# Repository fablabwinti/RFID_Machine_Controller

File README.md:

# RFID_Machine_Controller
This repository contains the hardware design files (eagle) and the firmware (Arduino) for the Fablab Winti RFID machine access controller. 
## Hardware features
- Based on ESP8266 so it has direct access to WiFi
- RFID reader 
- OLED display
- Piezo buzzer
- Multi-color LED
- SD card for event logging
- RTC for accurate time keeping without network access
- Isolated output with screw terminal
  - Option 1: Relay output: 250V, 5A, NC or NO with a 5x20mm fuse
  - Option 2: Opto-coupled output (50V, 40mA)
- Input voltage: 5V ±0.5V with input protection (reverse voltage protection, overvoltage protection)
- Three input connecters: 5.5x2.1mm DC jack, Micro USB jack, screw termianl

## Firmware features
- Easy web based configuration
- Time sync through NTP
- Automatic synchronization of local RTC 
- Automatic update of user database from server
- Local storage of access rights: works during network failures
- Local data logging to SD-Card or Flash (TBD)
- Transmit log data to server as soon as it is available

## Arduino IDE
### Add Board to IDE
File -> Preferences -> Settings -> Additional boards manager URLs: http://arduino.esp8266.com/stable/package_esp8266com_index.json  
### Install Board
Tools -> Boards -> Boards Manager
Search for "esp8266" and install it
### Select Board
Tools -> Boards -> esp8622 -> "Generic ESP8622 Module"
### Board Configurations
Select the following settings under "Tools"

### Install Libraries
Unzip "FabLabRFID_Library.zip" in the arduino library folder:

- Windows: `C:\Users\{username}\Documents\Arduino`
- macOS: `/Users/{username}/Documents/Arduino`
- Linux: `/home/{username}/Arduino`

#### Manually

Tools -> Manage Libraries

Install all libraries as described in Fablab_RFID_control.ino, line 52 to 70 (?)

MRFC522: Download from git (https://github.com/miguelbalboa/rfid) and add it to the library (.../Documents/Arduino/Libraries/...)

## Upload Flash Content

The `spiffs_flash.py` script automatically builds the SPIFFS filesystem image from the `data` directory and uploads it to the ESP8266.

### Prerequisites
- Python 3.x installed
- ESP8266 connected via USB
- Arduino15 directory present (auto-detected or manually specified)

### Usage

Basic upload (auto-detects Arduino15 directory):
```bash
python spiffs_flash.py --port COM8
```

With custom options:
```bash
# Specify Arduino15 directory manually
python spiffs_flash.py --port COM8 --arduino-root "C:\Users\YourName\AppData\Local\Arduino15"

# Erase SPIFFS region before writing (if write fails)
python spiffs_flash.py --port COM8 --erase-region

# Keep temporary build files for inspection
python spiffs_flash.py --port COM8 --keep-temp

# Use existing .bin file (skip build)
python spiffs_flash.py --port COM8 --bin path\to\existing.spiffs.bin
```

### Troubleshooting
- If Arduino15 not found, the script will prompt for the path
- Use `--erase-region` if you encounter write errors (preserves main firmware)
- Change COM port number to match your device (check Device Manager on Windows)

# License
-Firmware under GNU LGPL Version 3
-Hardware under Creative Commons 4.0 license: CC-BY-SA

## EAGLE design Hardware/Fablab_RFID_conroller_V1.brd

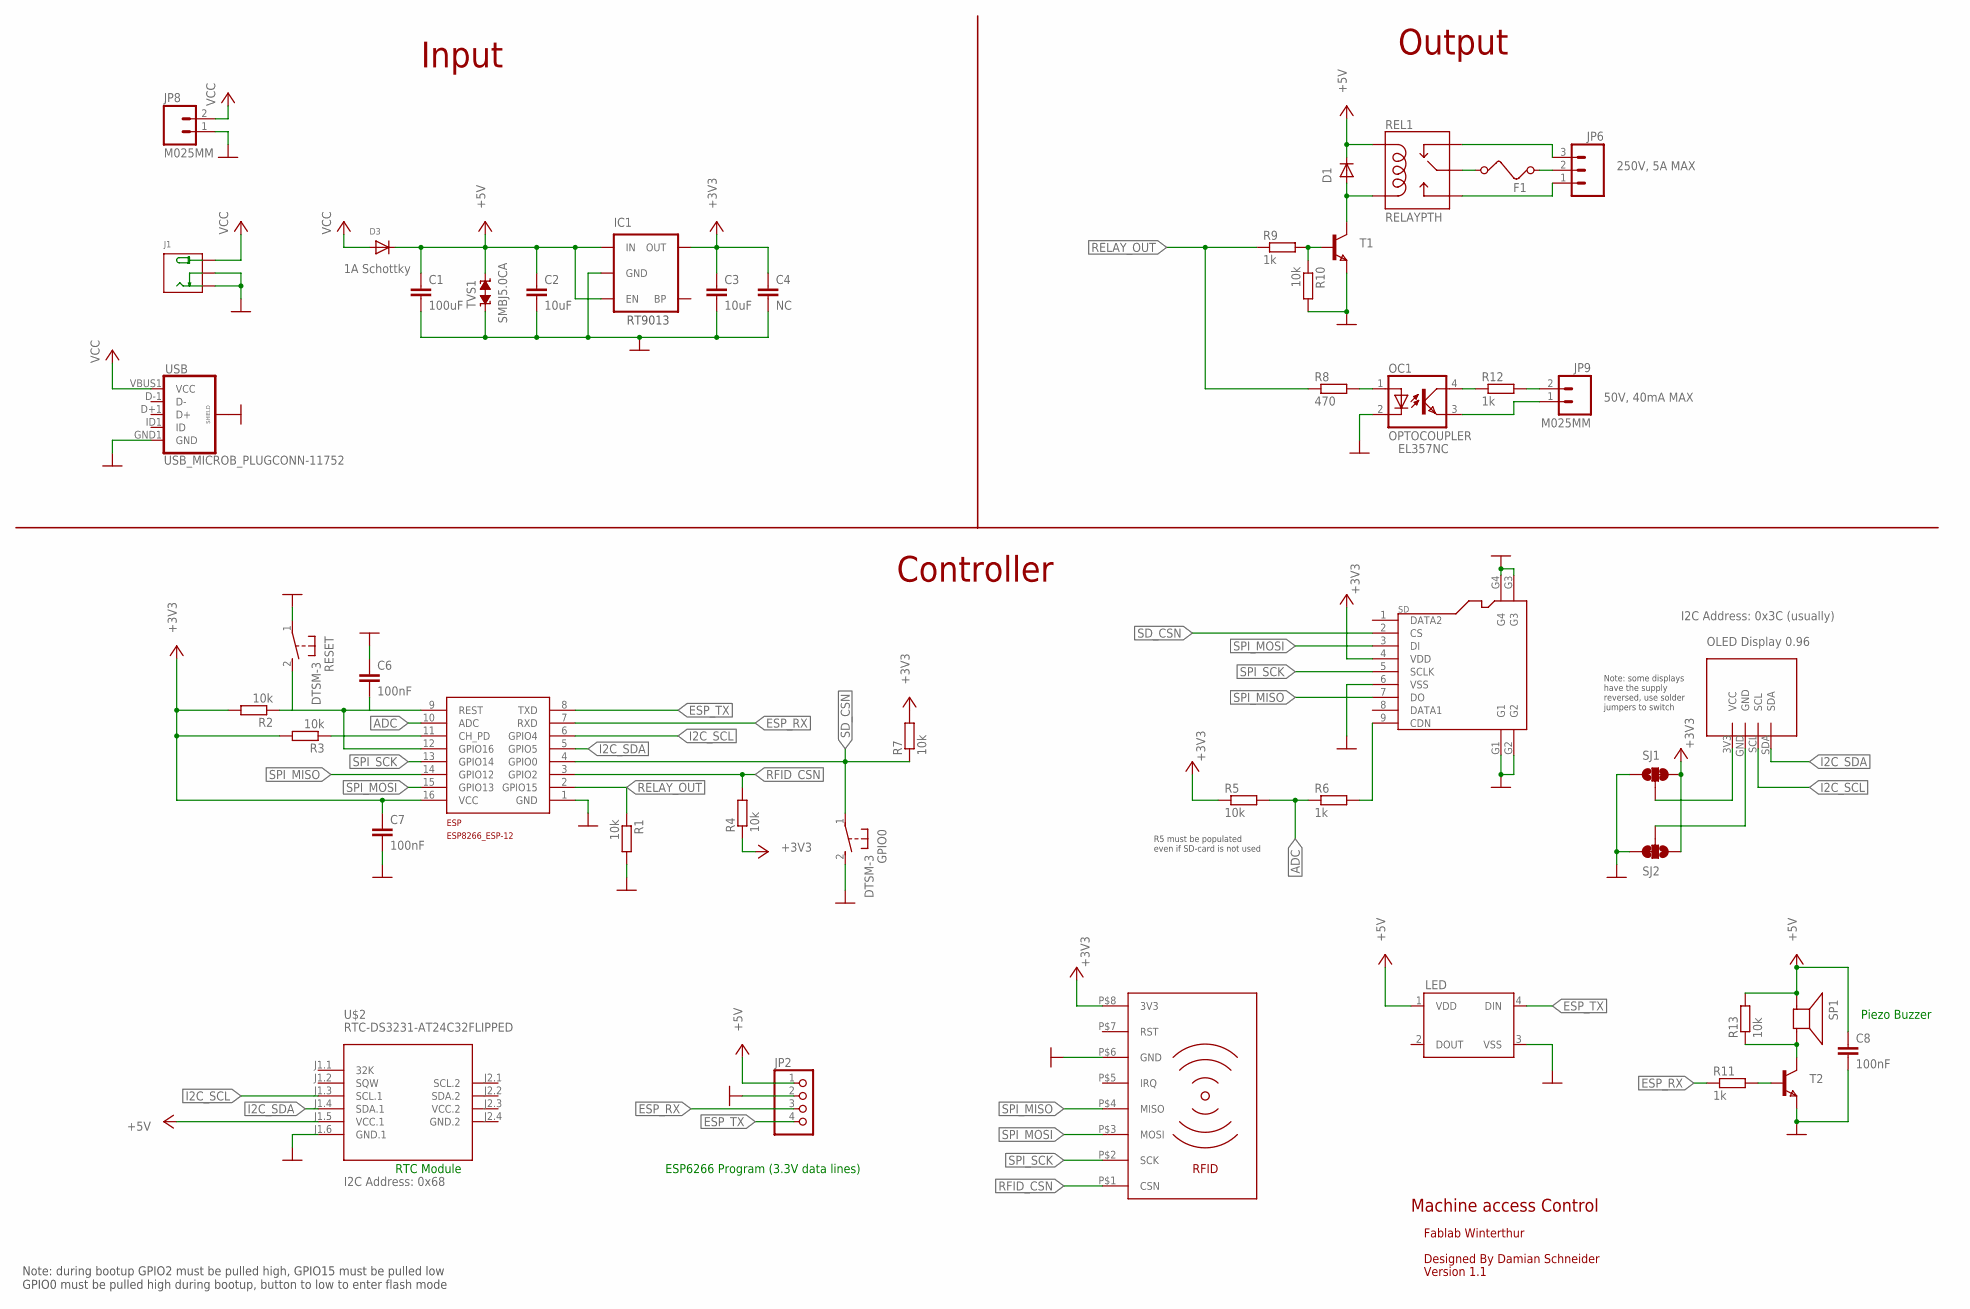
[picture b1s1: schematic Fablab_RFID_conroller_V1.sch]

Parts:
C1: 100uF; C1206
C2, C3: 10uF; C0805
C4: NC; C1206
C6, C7, C8: 100nF; C0603
D1: DIODE-MINIMELF; MINIMELF
D3: DIODESMA; SMADIODE
ESP: ESP8266_ESP-12; ESP8266-ESP12
F1: FUSE
GPIO0: DTSM-3
IC1: V_REG_LDOSMD; SOT23-5
J1: JACK-DC-3P-3410020P1; PW-3P-2.1
JP2: HEADER-1X476MIL; 1X04_ROUND_76
JP6: M03-SCREW-5MM; SCREWTERMINAL-5MM-3
JP8, JP9: M025MM; SCREWTERMINAL-5MM-2
LED: WS2812B
OC1: OPTOCOUPLER; SOP04
OLED: OLED_0.96_I2CNOHOLES; OLED_0.96_I2C_NOHOLES
R1, R2, R3, R4, R5, R7, R10, R13: 10k; R0603
R6, R9, R11: 1k; R0603
R8: 470; R0603
R12: 1k; R0805
REL1: RELAYPTH; SRD-05VDC-SL-C
RESET: DTSM-3
RFID: RFID_MODULE_RC522; RFID-RC522-MODULE
SD: MICRO-SDCARD-CONNECTOR-3300060P1; 9P-SMD-W-RING
SJ1, SJ2: JUMPER-PAD-3-2OF3_NC_BY_TRACE_LARGE; PAD-JUMPER-3-2OF3_NC_BY_TRACE_YES_SILK_LARGE
SP1: SPEAKER/AL60P; AL60P
T1, T2: NPNSOT23; SOT-23
TVS1: TVS-SMBJ; SMBJ
U$2: RTC-DS3231-AT24C32FLIPPED; RTC-DS3231_FLIPPED
USB: USB_MICROB_PLUGCONN-11752; USB-B-MICRO-SMD_V03

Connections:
!SDCARD_DETECT: R6.2, SD.9 (CDN)
+3V3: C3.1, C4.1, C7.1, ESP.16 (VCC), IC1.5 (OUT), R2.2, R3.2, R4.1, R5.1, R7.2, RFID.P$8 (3V3), SD.4 (VDD), SJ1.3, SJ2.1
+5V: C1.1, C2.1, C8.1, D1.C, D3.C, IC1.1 (IN), IC1.3 (EN), JP2.1, LED.1 (VDD), R13.2, REL1.COIL1, SP1.1 (+), TVS1.C (2), U$2.J1.5 (VCC.1)
ADC: ESP.10 (ADC), R5.2, R6.1
CHPD: ESP.11 (CH_PD), R3.1
ESP_RX: ESP.7 (RXD), JP2.3, R11.1
ESP_TX: ESP.8 (TXD), JP2.4, LED.4 (DIN)
GND: C1.2, C2.2, C3.2, C4.2, C6.1, C7.2, C8.2, ESP.1 (GND), GPIO0.2, IC1.2 (GND), J1.-1 (-), J1.-2 (CDN), JP2.2, JP8.1, LED.3 (VSS), OC1.2 (C), R1.2, R10.2, RESET.1, RFID.P$6 (GND), SD.6 (VSS), SD.G1, SD.G2, SD.G3, SD.G4, SJ1.1, SJ2.3, T1.2 (E), T2.2 (E), TVS1.A (1), U$2.J1.6 (GND.1), USB.GND1 (GND), USB.SHIELD1 (SHIELD), USB.SHIELD2 (SHIELD), USB.SHIELD3 (SHIELD)
GND.2: U$2.J2.4 (GND.2)
I2C_SCL: ESP.6 (GPIO4), OLED.SCL, U$2.J1.3 (SCL.1)
I2C_SDA: ESP.5 (GPIO5), OLED.SDA, U$2.J1.4 (SDA.1)
unnamed: JP9.2, R12.2
unnamed: OLED.3V3 (VCC), SJ1.2
unnamed: OLED.GND, SJ2.2
unnamed: R9.2, R10.1, T1.3 (B)
unnamed: D1.A, REL1.COIL0, T1.1 (C)
unnamed: R13.1, SP1.2 (-), T2.1 (C)
unnamed: R11.2, T2.3 (B)
unnamed: F1.1, JP6.2
unnamed: JP6.1, REL1.SW_NO (SWOPEN)
unnamed: F1.2, REL1.SWCOMMON
unnamed: JP6.3, REL1.SW_NC (SWCLOSE)
unnamed: OC1.1 (A), R8.2
unnamed: OC1.4 (COL), R12.1
unnamed: JP9.1, OC1.3 (EMIT)
RELAY_OUT: ESP.2 (GPIO15), R1.1, R8.1, R9.1
RESET: C6.2, ESP.9 (REST), ESP.12 (GPIO16), R2.1, RESET.2
RFID_CSN: ESP.3 (GPIO2), R4.2, RFID.P$1 (CSN)
SD_CSN: ESP.4 (GPIO0), GPIO0.1, R7.1, SD.2 (CS)
SPI_MISO: ESP.14 (GPIO12), RFID.P$4 (MISO), SD.7 (DO)
SPI_MOSI: ESP.15 (GPIO13), RFID.P$3 (MOSI), SD.3 (DI)
SPI_SCK: ESP.13 (GPIO14), RFID.P$2 (SCK), SD.5 (SCLK)
VCC: D3.A, J1.+, JP8.2, USB.VBUS1 (VCC)
VCC.2: U$2.J2.3 (VCC.2)

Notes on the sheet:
ESP6266 Program (3.3V data lines)
Note: during bootup GPIO2 must be pulled high, GPIO15 must be pulled low GPIO0 must be pulled high during bootup, button to low to enter flash mode
Piezo Buzzer
OLED Display 0.96
R5 must be populated even if SD-card is not used
RTC Module
RT9013
Machine access Control
Fablab Winterthur
Designed By Damian Schneider
EL357NC
50V, 40mA MAX
250V, 5A MAX
I2C Address: 0x68
I2C Address: 0x3C (usually)
1A Schottky
SMBJ5.0CA
Input
Output
Controller
Note: some displays have the supply reversed, use solder jumpers to switch
Version 1.1

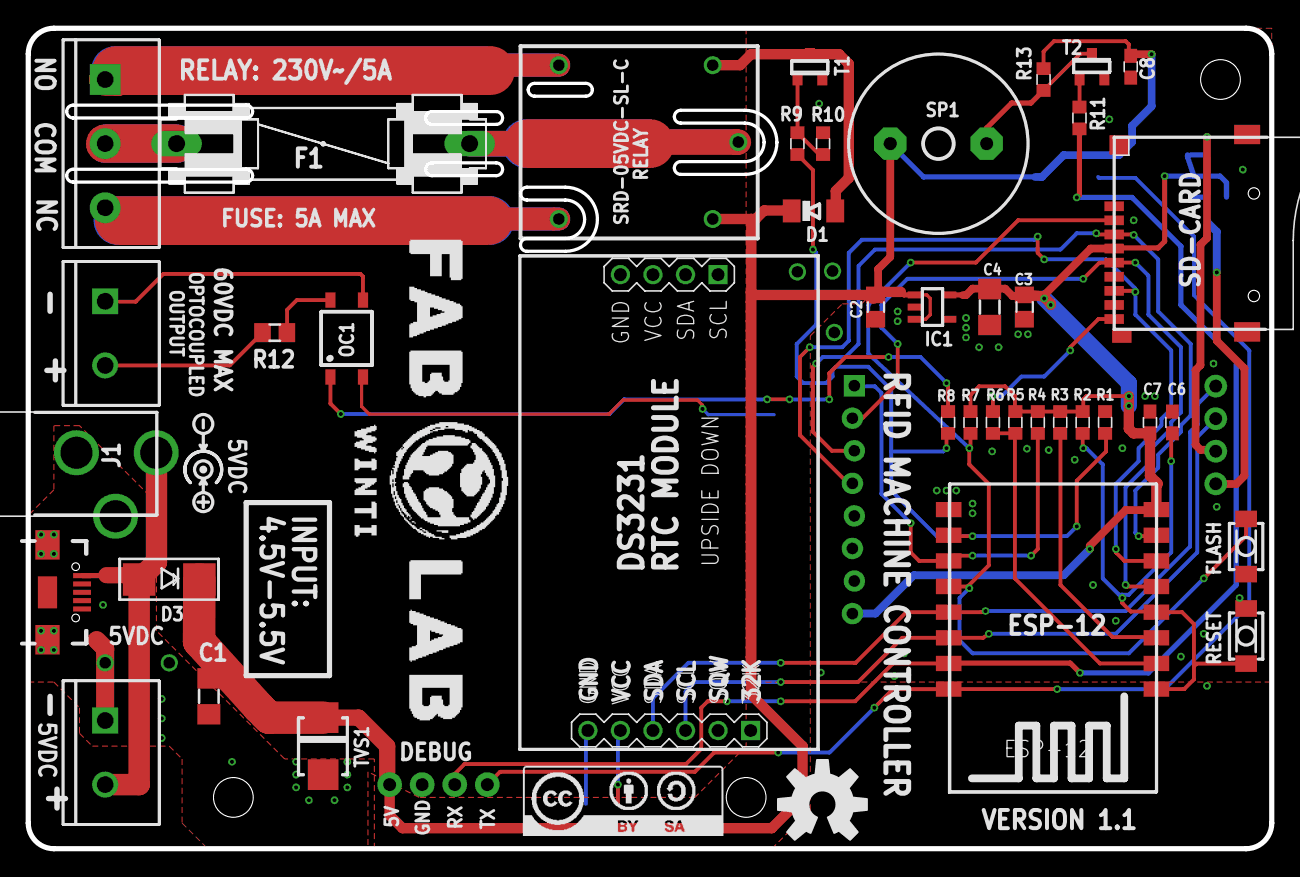
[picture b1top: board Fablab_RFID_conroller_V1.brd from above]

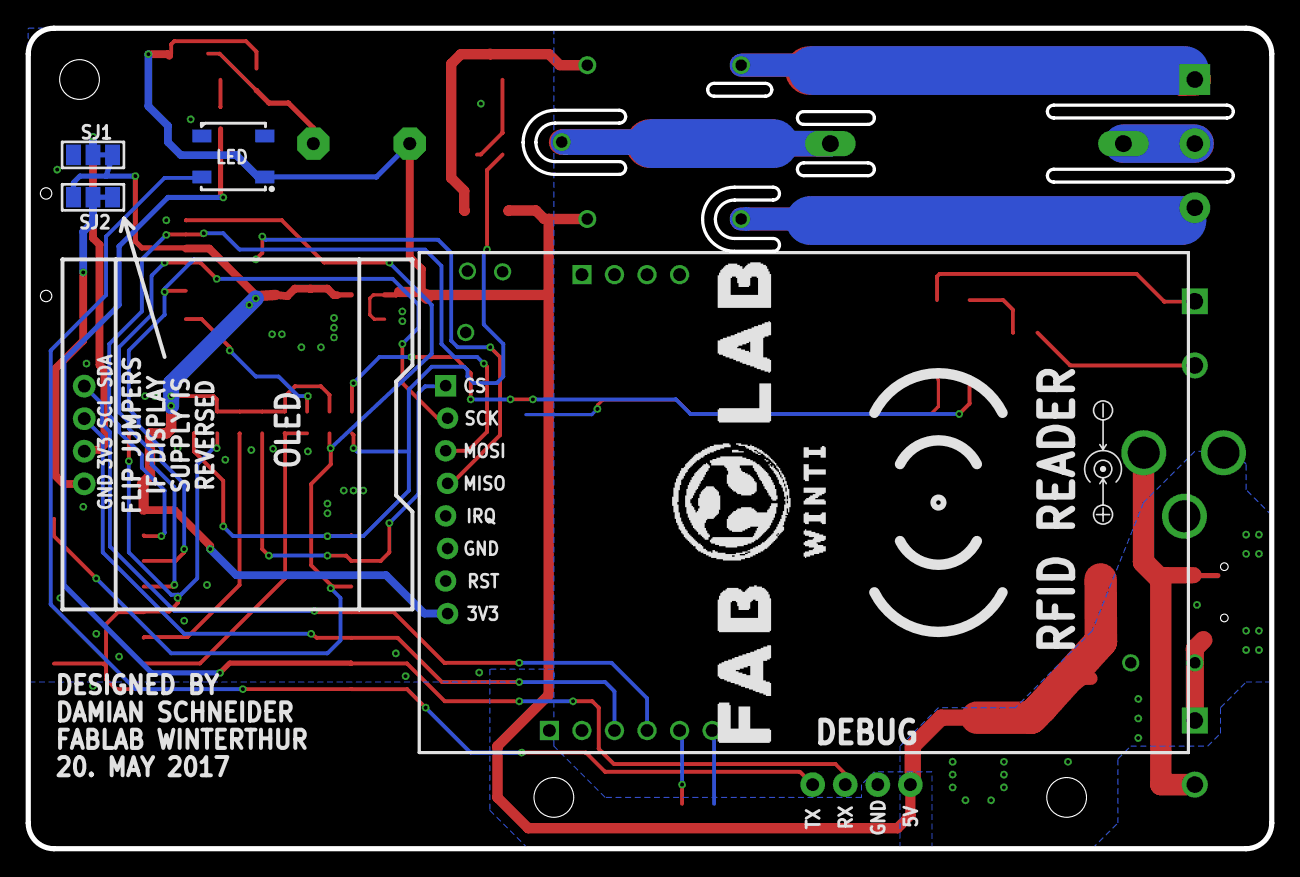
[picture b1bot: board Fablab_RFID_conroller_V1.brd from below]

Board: 2 copper layers, 97.0 x 64.0 mm, 47 parts (5 on the bottom side), 32 nets.

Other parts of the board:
U$6: OSHW-LOGO-L

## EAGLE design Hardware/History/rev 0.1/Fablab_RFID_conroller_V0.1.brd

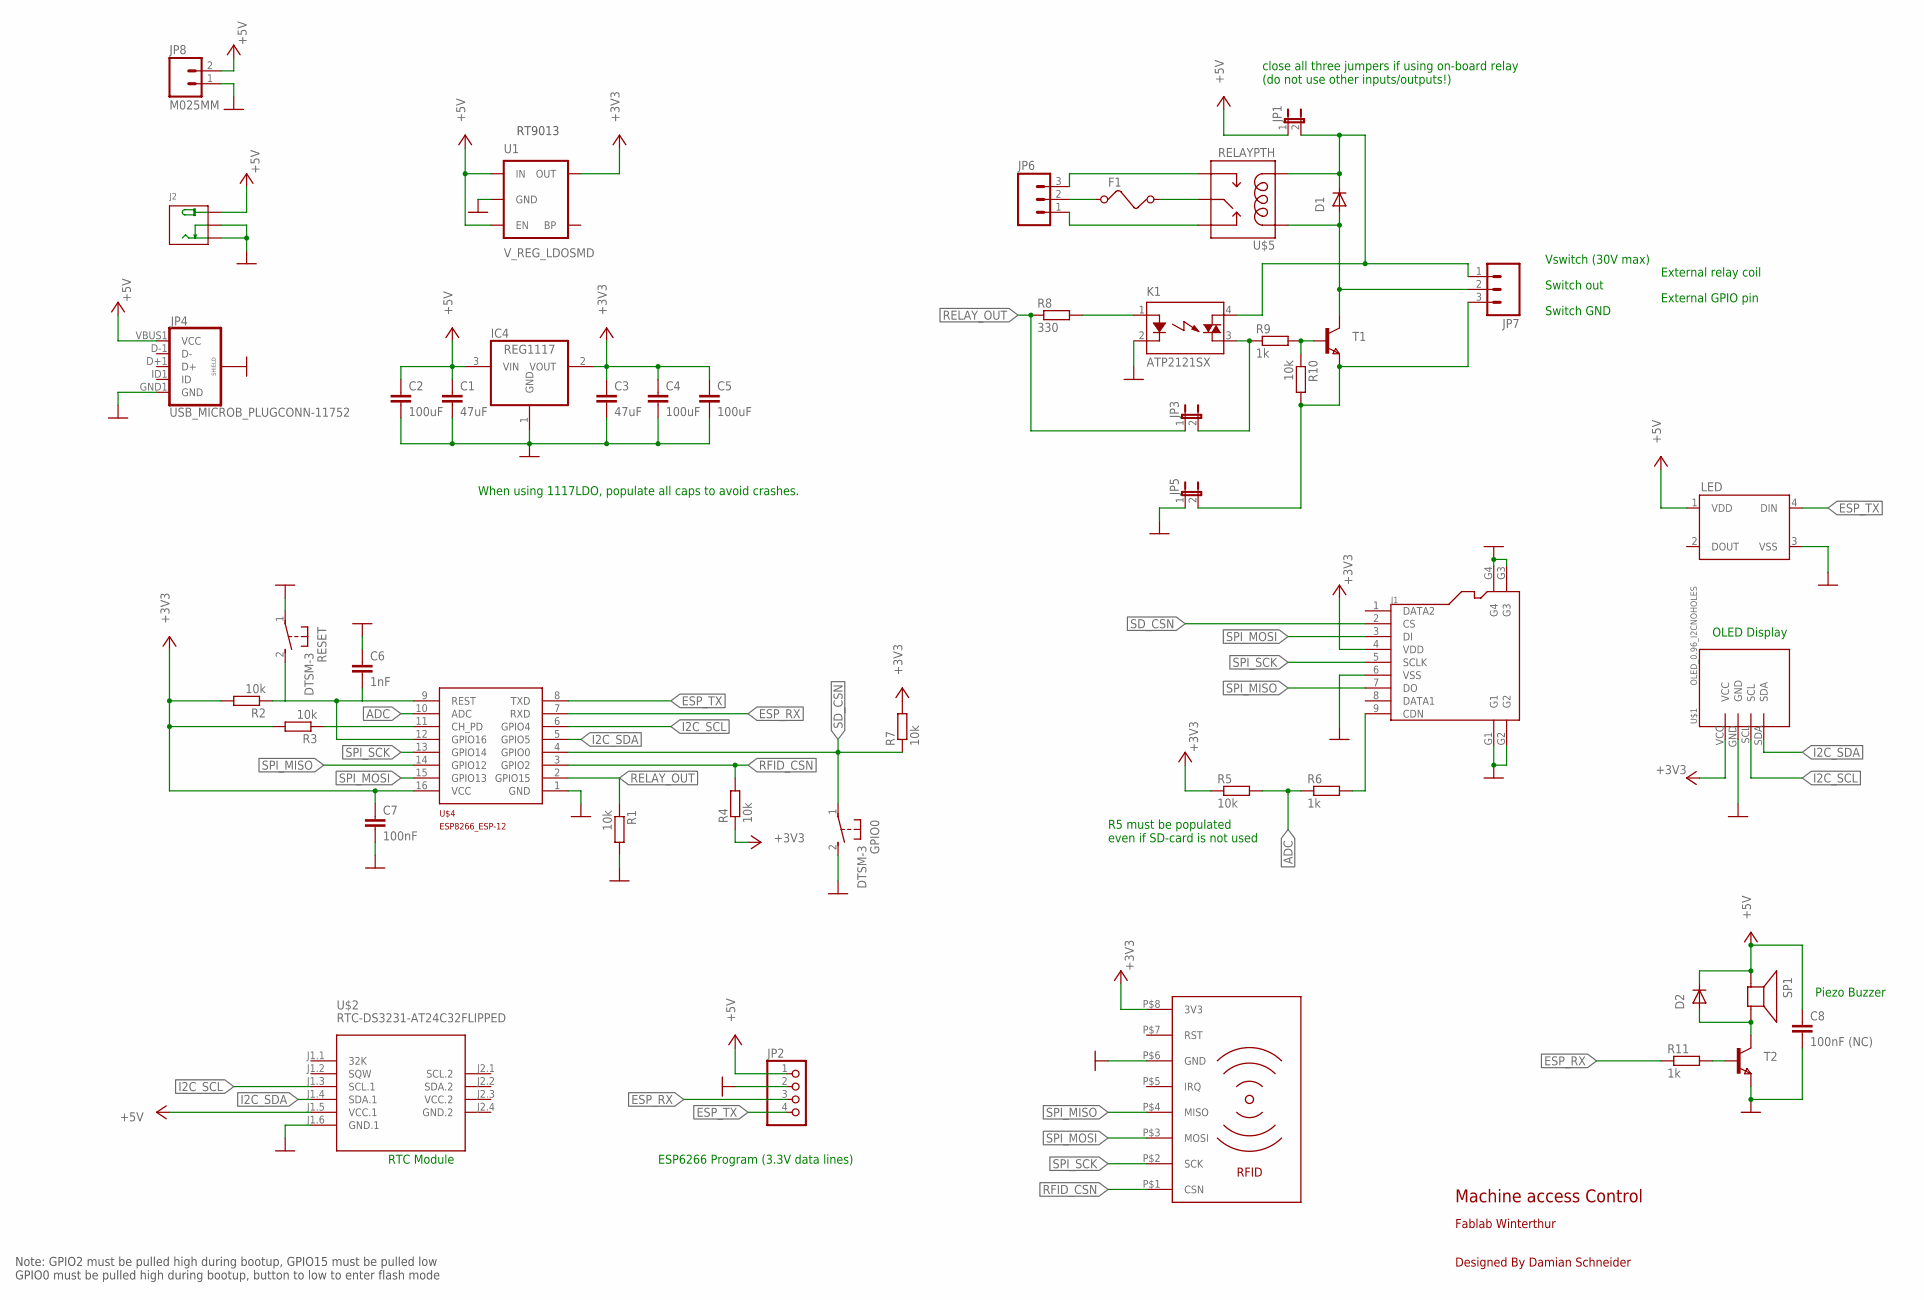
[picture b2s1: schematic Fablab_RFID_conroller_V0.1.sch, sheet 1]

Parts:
C1, C3: 47uF; C0805
C2, C4, C5: 100uF; C1206
C6: 1nF; C0603
C7: 100nF; C0603
C8: 100nF (NC); C0603
D1, D2: DIODE-MINIMELF; MINIMELF
F1: FUSE
GPIO0: DTSM-3
IC4: REG1117; SOT223
J1: MICRO-SDCARD-CONNECTOR-3300060P1; 9P-SMD-W-RING
J2: JACK-DC-3P-3410020P1; PW-3P-2.1
JP1, JP3, JP5: JP1E; JP1
JP2: HEADER-1X476MIL; 1X04_ROUND_76
JP4: USB_MICROB_PLUGCONN-11752; USB-B-MICRO-SMD_V03
JP6, JP7: M03-SCREW-5MM; SCREWTERMINAL-5MM-3
JP8: M025MM; SCREWTERMINAL-5MM-2
K1: ATP2121SX; SOP04
LED: WS2812B
R1, R2, R3, R4, R5, R7, R10: 10k; R0603
R6, R9, R11: 1k; R0603
R8: 330; R0603
RESET: DTSM-3
SP1: SPEAKER/AL60P; AL60P
T1, T2: NPNSOT23; SOT-23
U1: V_REG_LDOSMD; SOT23-5
U$1: OLED_0.96_I2CNOHOLES; OLED_0.96_I2C_NOHOLES
U$2: RTC-DS3231-AT24C32FLIPPED; RTC-DS3231_FLIPPED
U$3: RFID_MODULE_RC522; RFID-RC522-MODULE
U$4: ESP8266_ESP-12; ESP8266-ESP12
U$5: RELAYPTH; SRD-05VDC-SL-C

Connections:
!SDCARD_DETECT: J1.9 (CDN), R6.2
+3V3: C3.1, C4.1, C5.1, C7.1, IC4.2 (VOUT), J1.4 (VDD), R2.2, R3.2, R4.1, R5.1, R7.2, U1.5 (OUT), U$1.VCC, U$3.P$8 (3V3), U$4.16 (VCC)
+5V: C1.1, C2.1, C8.1, D2.C, IC4.3 (VIN), J2.+, JP1.1, JP2.1, JP4.VBUS1 (VCC), JP8.2, LED.1 (VDD), SP1.1 (+), U1.1 (IN), U1.3 (EN), U$2.J1.5 (VCC.1)
ADC: R5.2, R6.1, U$4.10 (ADC)
CHPD: R3.1, U$4.11 (CH_PD)
ESP_RX: JP2.3, R11.1, U$4.7 (RXD)
ESP_TX: JP2.4, LED.4 (DIN), U$4.8 (TXD)
GND: C1.2, C2.2, C3.2, C4.2, C5.2, C6.1, C7.2, C8.2, GPIO0.2, IC4.1 (GND), J1.6 (VSS), J1.G1, J1.G2, J1.G3, J1.G4, J2.-1 (-), J2.-2 (CDN), JP2.2, JP4.GND1 (GND), JP4.SHIELD1 (SHIELD), JP4.SHIELD2 (SHIELD), JP4.SHIELD3 (SHIELD), JP5.1, JP8.1, LED.3 (VSS), R1.2, RESET.1, T2.2 (E), U1.2 (GND), U$1.GND, U$2.J1.6 (GND.1), U$3.P$6 (GND), U$4.1 (GND)
GND.2: U$2.J2.4 (GND.2)
I2C_SCL: U$1.SCL, U$2.J1.3 (SCL.1), U$4.6 (GPIO4)
I2C_SDA: U$1.SDA, U$2.J1.4 (SDA.1), U$4.5 (GPIO5)
unnamed: K1.1 (A), R8.2
unnamed: JP3.2, K1.3 (DS2), R9.1
unnamed: R9.2, R10.1, T1.3 (B)
unnamed: D1.A, JP7.2, T1.1 (C), U$5.COIL1
unnamed: JP5.2, JP7.3, R10.2, T1.2 (E)
unnamed: D2.A, SP1.2 (-), T2.1 (C)
unnamed: JP1.2, JP7.1, K1.4 (DS1)
unnamed: D1.C, U$5.COIL0
unnamed: R11.2, T2.3 (B)
unnamed: F1.1, JP6.2
unnamed: JP6.3, U$5.SW_NO (SWOPEN)
unnamed: F1.2, U$5.SWCOMMON
unnamed: JP6.1, U$5.SW_NC (SWCLOSE)
RELAY_OUT: JP3.1, R1.1, R8.1, U$4.2 (GPIO15)
RESET: C6.2, R2.1, RESET.2, U$4.9 (REST), U$4.12 (GPIO16)
RFID_CSN: R4.2, U$3.P$1 (CSN), U$4.3 (GPIO2)
SD_CSN: GPIO0.1, J1.2 (CS), R7.1, U$4.4 (GPIO0)
SPI_MISO: J1.7 (DO), U$3.P$4 (MISO), U$4.14 (GPIO12)
SPI_MOSI: J1.3 (DI), U$3.P$3 (MOSI), U$4.15 (GPIO13)
SPI_SCK: J1.5 (SCLK), U$3.P$2 (SCK), U$4.13 (GPIO14)
VCC.2: U$2.J2.3 (VCC.2)

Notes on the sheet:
ESP6266 Program (3.3V data lines)
Note: GPIO2 must be pulled high during bootup, GPIO15 must be pulled low GPIO0 must be pulled high during bootup, button to low to enter flash mode
Piezo Buzzer
OLED Display
R5 must be populated even if SD-card is not used
RTC Module
Vswitch (30V max)
Switch GND
Switch out
External relay coil
External GPIO pin
close all three jumpers if using on-board relay (do not use other inputs/outputs!)
RT9013
When using 1117LDO, populate all caps to avoid crashes.
Machine access Control
Fablab Winterthur
Designed By Damian Schneider

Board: 2 copper layers, 46 parts (3 on the bottom side), 30 nets, no tracks yet.

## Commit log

2017-06-03 updated readme with license
2017-06-03 Initial project commit
    PCB rev. 1 is done but not veryfied, license for hardware added
2017-06-03 license to markdown
2017-06-03 remove obsolete file
2017-06-04 add SD card to BOM
2017-06-04 initial firmware commit
    just basic functionality and lots of debugging messages, not really
    useable yet
2017-06-11 removed OTA support, changed LED behaviour
    OTA was replaced by secure web update
2017-06-11 removed watchdog timer
    it conflicts somehow with the fastled library. also the controller
    should never atuomatically reboot
2017-06-11 rename
2017-06-11 sound support for final version
    changed pin from debug to final, added login and logout sound, changed
    function names
2017-06-11 reorganized timer management
    RTC runs on epoch (UNIX) time, local clock runs on local time, including
    timezone and automatic DST (europe)
2017-06-11 add display support on init
2017-06-11 code rearranged
2017-06-11 big update on display support
    -adding logo
    -adding proper display during login/logout
    -added time on the display
2017-06-11 huge update
    -added functionality to properly login/logout
    -not accepting any cards while logged in except the user who logged in
    -improved user handling
2017-06-11 led support and global variable added
2017-06-11 remove OTA
2017-06-11 changed to fastled library, code cleanup
2017-06-11 update on used libraries and code cleanup
    also adding display support during bootup
2017-08-15 Major update: local database now loaded from server
    -added server connectivity (working)
    -updated local user database to match server (working)
    -added display name from database
    -preliminary implemenation of SD card database for events
    -added event handling (incomplete)
    -added JSON library for endoding and decoding
2017-08-17 added event generation functions
    and debugged SD card database saving, now fully working
    also added proper timestamp string generation
    plus some small bugfixes
2017-08-20 started updating config stuff, started on RFID advanced auth
    -added handling of more eeprom config variables
    -added support to make all config page traffic websocket based (webpage
    still needs updating)
    -changed server sendouts to use data from config (no more fixed strings)
    -added password support for config page access
    -cleaned up the todo list
2017-08-22 Bugfixes & Working on Config Webpage
    trying to get the config page up to speed, partially working but still
    work in progress
2017-08-24 finished direct database request of machine names
    MID and MNAME are added to the option select menu, a manual menu is
    shown if connection fails.
2017-08-26 big config page update
    -fixed some bugs on webpage and in firmware
    -added config support
    -website now downloads machine list from server automatically
    -changed ajax loader.gif
    -added firmware and spiffs image file update directly from the server
    (triggered on config page)
2017-08-26 updated schematic with errata
2017-08-26 removed update server
    it is no longer needed thanks to http update
2017-09-08 bugfixes & cosmetics
2017-12-30 RFID and config Update
    - added framework for RFID authentication using the access key and a
    passphrase saved on the card, configurable on the webpage
    -Added a few variables to the config
    -Made web page credentials configurable
    -Prepared for the use of an API key, it can be entered on the webpage
    -changed factory reset: can now be done before any code runs, as a
2018-01-21 updated for new server version
    -changed api URI to /api/...
    -changed event number definitions
    -added error logs
    -added logs for unsuccessful tag access
    -updated BOM
    -added tag time verification
2018-01-21 display layout update
    fonts added, some useful, some not
2018-01-23 bugfix: writing to nonexisting SD card no more
2018-01-25 added status icons
    also added som additional compiling info, it now works on arduino 1.8.5
    with ESP version 2.4.0 (which it did not before, not sure what change
    made that possible)
    Status icons is work in progress.
2018-07-16 Add missing global variable.
2018-07-16 Add hand-drawn fonts and replace all use of other small fonts by them.
2018-07-16 Fix status icons.
    The previous ones only displayed pixel garbage for me.
2018-07-16 Add checkmark/cross icons to transition screens.
2018-08-12 refactoring & minor fixes
    forgot to commit for a long time... only minor code changes
2018-08-12 fixed errors after merging pull request
    also made server connection timeout shorter to avoid long delays in
    login if server is not available
2018-11-25 minor bugfixes
    -added login/logout function of admin tag also during a websocket
    session
2019-04-29 stability update and added post logout switch delay
    disabling wifi during login times to increase stability (hopefully). had
    to add a delay before disabling wifi or it would crash very often...
    also some minor bugfixes here and there.
2019-05-01 stability improvement added post logout user data display
    disabled software watchdog,
    improved sendout/sd saving handling
    after logout, time is still displayed for 10 sec
    no more crashes (so far) when disabling wifi
2019-05-12 major update, added fatfs, added new way of secure connection, added more machine options
    plus some code cleanup, stability improvement yet again, added log to SD
    card every time interval. still need to do price calculation but
    everything is prepared for that.
2019-05-12 changed to normal EDB again, fork was fully code compatible
2019-05-12 updated SD stuff
2019-05-15 added price calculation
2019-06-22 updated event database, added key read from spiffs
    -event database is now also in spiffs, can be put on SD card by changing
    a define
    -public key (pem) is read from file in spiffs so it can be configured in
    real time (not yet implemented)
2020-02-04 added ssh file handling with public key
    upload may not yet work through webpage but works through direct spiffs
    upload
2020-02-23 update for arduinojson v 6.x
    updated to use new version of arduinojson
2020-02-25 update serial
2020-02-25 add fablab pem key file
2020-02-28 bugfix in json parsing
2020-02-29 typo
2020-03-07 LED update bugfix, Serial debug output refactor
2023-12-26 Fix use of uninitialized variable.
    It could randomly cause logs to be sent to the server without a tid.
2023-12-26 Send log events to the server in the order they were created.
    The previous partly-reversed order made it hard to interpret them on the server when timestamps were not chronological due to network time updates or RTC failure.
    The database in SPIFFS and the queue in RAM, in that order, now form a combined FIFO queue. Entries are sent to the server directly from the RAM queue if possible, but if not, moved to the flash data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
2023-12-28 Fix failing database update with 4 or more user entries.
    Trying to parse up to 5 entries at once did not work, it already ran into a NoMemory error at 4 fully specified entries with the 512 byte document buffer. Parse them one by one instead, following htt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
2024-05-09 Address erratum: Fix +5V connection of relay coil.
2024-05-09 Address erratum: Replace diode D2 by 10k resistor R13.
2024-05-09 Regenerate PDF and Gerber files for version 1.1.
2024-10-22 Observe the minimum periods price for the cost display.
    Adjust to the current server that provides this field in the machine database.
    The additional configuration field requires introducing versioning in the EEPROM data structure.
2024-11-19 Remove unused files.
2025-11-12 KiCad transfer
    New KiCad Project, contains old Eagle Project (not tested yet)
2025-11-24 Update library version comments to the ones that work for me.
2025-11-24 added library files + spiffs_flash.py
2026-04-30 docs: add Docs/ folder and AiTasks with current firmware documentation

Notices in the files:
parts and their libraries:
SparkFun-LED: Licensing: Creative Commons ShareAlike 4.0 International - https://creativecommons.org/licenses/by-sa/4.0
microbuilder: This work is placed in the public domain, and may be freely used for commercial and non-commercial work with the following conditions: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
